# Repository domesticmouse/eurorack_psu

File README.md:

# Eurorack PSU

A simple 6HP +-12V Eurorack PSU, based on Winterbloom's [Micronova][].
See [EurorRack dimensions][] for faceplate dimensions.

[Micronova]: https://winterbloom.com/shop/micronova/
[EurorRack dimensions]: https://midisoft.de/EuroRackDimensions/EuroRack_Dimensions.html

## Parts

| LCSC Part | Manufacturer | Description |
| --- | --- | --- |
| [C72487](https://www.lcsc.com/product-detail/C72487.html) | ROQANG | CAP ALUM 10uF ±20% 50V SMD |
| [C3001207](https://www.lcsc.com/product-detail/C3001207.html) | ROQANG | CAP ALUM 22uF ±20% 25V SMD |
| [C1779](https://www.lcsc.com/product-detail/C1779.html) | Samsung Electro-Mechanics | CAP CER 4.7uF 25V X5R 0805 |
| [C3151829](https://www.lcsc.com/product-detail/C3151829.html) | ROQANG | CAP ALUM 100uF ±20% 50V SMD |
| [c701168](https://www.lcsc.com/product-detail/C701168.html) | muRata | FIXED IND 10uH 800mA 190mΩ SMD,3x3mm |
| [c64982](https://www.lcsc.com/product-detail/C64982.html) | MDD(Microdiode Semiconductor) | DIODE SCHOTTKY 40V SMA(DO-214AC) |
| [C5369648](https://www.lcsc.com/product-detail/C5369648.html) | YLPTEC | K7812-1000R3 SIP,11.5x7.6mm AC DC Configurable Power Supply Modules RoHS |
| [C22355851](https://www.lcsc.com/product-detail/C22355851.html) | DOWO | VARISTOR 18V 150A 1206 |
| [C142805](https://www.lcsc.com/product-detail/C142805.html) | Littelfuse | 24V 1.5A 20A 3A 40mΩ 1812 PTC Resettable Fuses RoHS |
| [C27834](https://www.lcsc.com/product-detail/C27834.html) | UNI-ROYAL | RES 5.1kΩ ±1% 125mW 0805 |
| [C84256](https://www.lcsc.com/product-detail/C84256.html) | NATIONSTAR | LED RED 0805 SMD |
| [C22373734](https://www.lcsc.com/product-detail/C22373734.html) | Hynetek | USB-C Power Receiver Controller 100W |
| [C1744](https://www.lcsc.com/product-detail/C1744.html) | FH | 50V 4.7nF X7R ±10% 0805 |
| [C1726](https://www.lcsc.com/product-detail/C1726.html) | FH | 50V 20nF X7R ±10% 0805 |
| [C52711227](https://www.lcsc.com/product-detail/C52711227.html) | HH | USB 2.0 5A Surface Mount Vertical 16P Female Type-C USB Connector |

## USB Type C PD Datasheets

- [C52711227 USB Connector](https://www.lcsc.com/datasheet/C52711227.pdf)
- [C22373734 USB Type-C Power Delivery Sink Controller](https://www.lcsc.com/datasheet/C22373734.pdf)

## Kicanvas

- [PSU](https://kicanvas.org/?github=https%3A%2F%2Fgithub.com%2Fdomesticmouse%2Feurorack_psu%2Fblob%2Fmain%2Fhardware%2FPSU%2FPSU.kicad_pro)
- [Faceplate](https://kicanvas.org/?github=https%3A%2F%2Fgithub.com%2Fdomesticmouse%2Feurorack_psu%2Fblob%2Fmain%2Fhardware%2Ffaceplate%2Ffaceplate.kicad_pro)

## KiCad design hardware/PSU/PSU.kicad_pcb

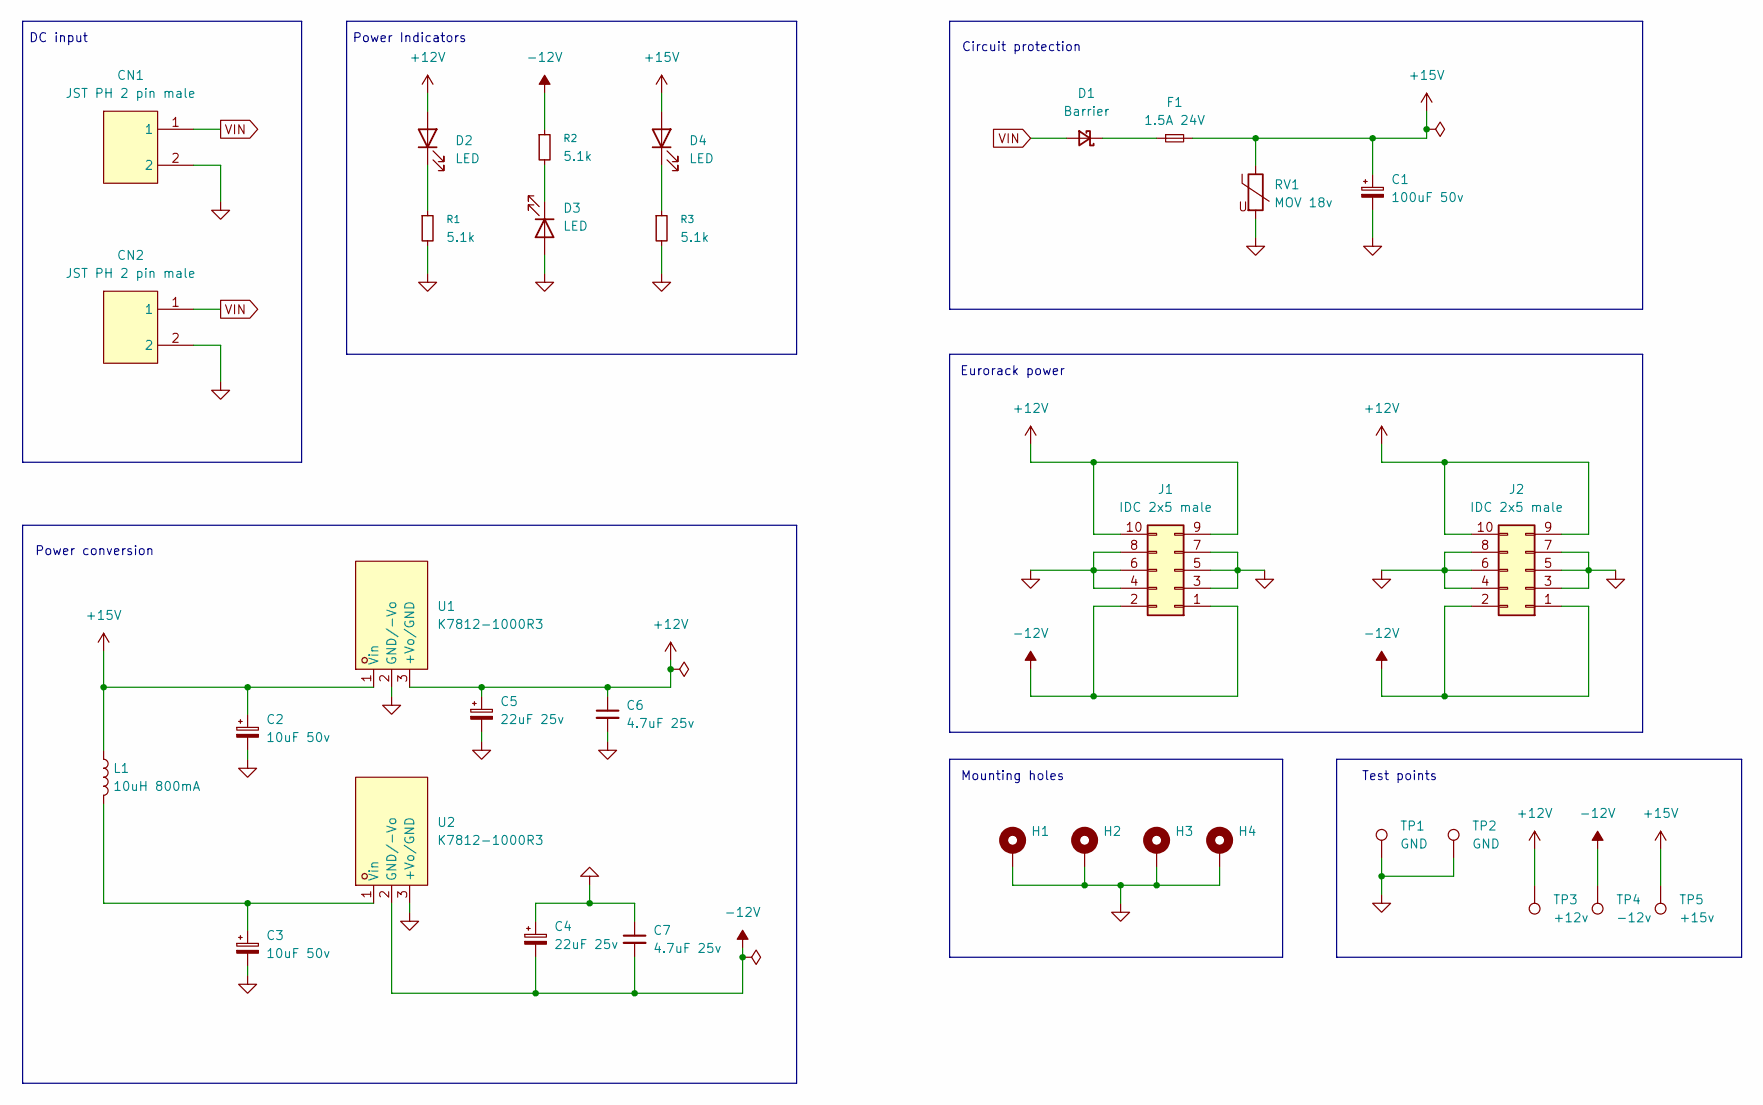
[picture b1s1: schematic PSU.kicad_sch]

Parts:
C1: 100uF 50v; CP_Elec_6.3x7.7; LCSC Part C3151829
C2, C3: 10uF 50v; CP_Elec_5x5.4; LCSC Part C72487
C4, C5: 22uF 25v; CP_Elec_5x5.4; LCSC Part C3001207
C6, C7: 4.7uF 25v; C_0805_2012Metric_Pad1.18x1.45mm_HandSolder; LCSC Part C1779
CN1, CN2: JST PH 2 pin male; CONN-TH_B2B-PH-K-S; LCSC Part C131337
D1: Barrier; D_SMA_Handsoldering; LCSC Part C64982
D2, D3, D4: LED; LED_D3.0mm; LCSC Part C84256
F1: 1.5A 24V; Fuse_1812_4532Metric_Pad1.30x3.40mm_HandSolder; LCSC Part C142805
H1, H2, H3, H4: MountingHole_3.2mm_M3_Pad
J1, J2: IDC 2x5 male; IDC-Header_2x05_P2.54mm_Vertical
L1: 10uH 800mA; L_muRata_LQH3NPZ100MMEL_HandSolder; LCSC Part C701168
R1, R2, R3: 5.1k; R_0805_2012Metric_Pad1.20x1.40mm_HandSolder; LCSC Part C27834
RV1: MOV 18v; R_1206_3216Metric_Pad1.30x1.75mm_HandSolder; LCSC Part C22355851
TP1, TP2: GND; TestPoint_Keystone_5000-5004_Miniature
TP3: +12v; TestPoint_Keystone_5000-5004_Miniature
TP4: -12v; TestPoint_Keystone_5000-5004_Miniature
TP5: +15v; TestPoint_Keystone_5000-5004_Miniature
U1, U2: K7812-1000R3; PWRM-TH_K7812-1000R3; LCSC Part C5369648

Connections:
+12V: C5.1, C6.1, D2.2 (A), J1.9, J1.10, J2.9, J2.10, TP3.1, U1.3 (+Vo/GND)
+15V: C1.1, C2.1, D4.2 (A), F1.2, L1.1, RV1.1, TP5.1, U1.1 (Vin)
-12V: C4.2, C7.2, J1.1, J1.2, J2.1, J2.2, R2.1, TP4.1, U2.2 (GND/-Vo)
GND: C1.2, C2.2, C3.2, C4.1, C5.2, C6.2, C7.1, CN1.2, CN2.2, D3.2 (A), H1.1, H2.1, H3.1, H4.1, J1.3, J1.4, J1.5, J1.6, J1.7, J1.8, J2.3, J2.4, J2.5, J2.6, J2.7, J2.8, R1.2, R3.2, RV1.2, TP1.1, TP2.1, U1.2 (GND/-Vo), U2.3 (+Vo/GND)
unnamed: D1.1 (K), F1.1
unnamed: D2.1 (K), R1.1
unnamed: D3.1 (K), R2.2
unnamed: D4.1 (K), R3.1
unnamed: C3.1, L1.2, U2.1 (Vin)
VIN: CN1.1, CN2.1, D1.2 (A)

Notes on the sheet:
Eurorack power
Circuit protection
Power Indicators
Test points
Mounting holes
DC input
Power conversion

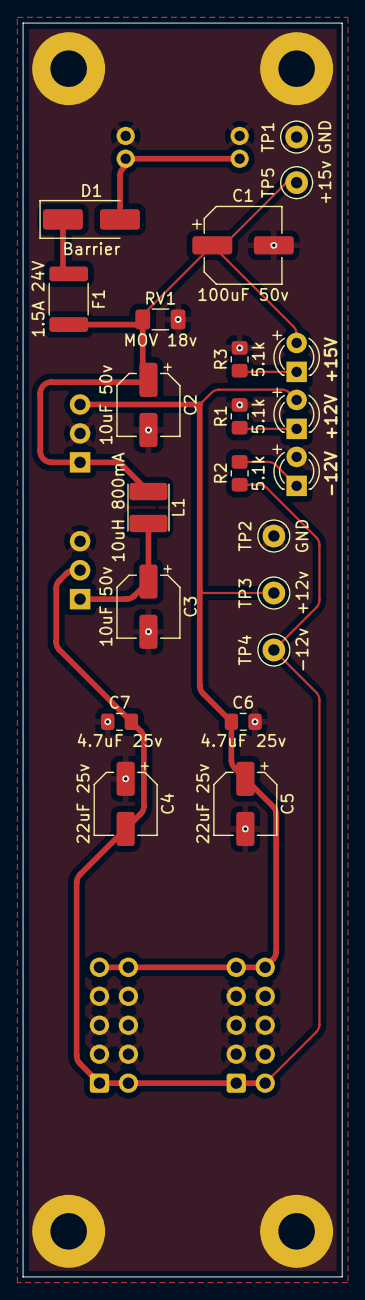
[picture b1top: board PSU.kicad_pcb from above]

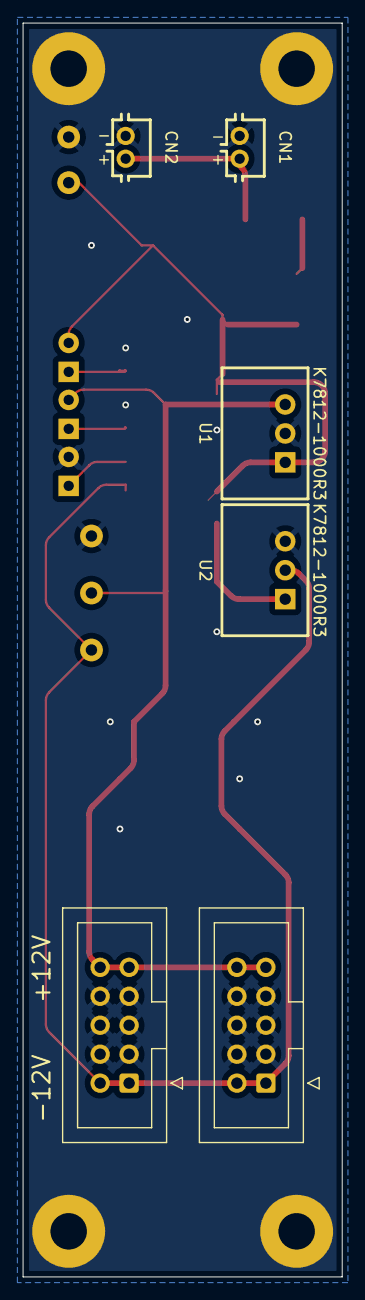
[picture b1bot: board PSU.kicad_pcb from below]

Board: 2 copper layers, 28.0 x 110.0 mm, 32 parts (6 on the bottom side), 10 nets.

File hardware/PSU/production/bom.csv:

Designator,Footprint,Quantity,Value,LCSC Part #
C1,CP_Elec_6.3x7.7,1,100uF 50v,C3151829
"C2, C3",CP_Elec_5x5.4,2,10uF 50v,C72487
"C4, C5",CP_Elec_5x5.4,2,22uF 25v,C3001207
"C6, C7",0805,2,4.7uF 25v,C1779
"CN1, CN2",CONN-TH_B2B-PH-K-S,2,JST PH 2 pin male,C131337
D1,D_SMA_Handsoldering,1,Barrier,C64982
"D2, D3, D4",LED_D3.0mm,3,LED,C84256
F1,1812,1,1.5A 24V,C142805
"J1, J2",IDC-Header_2x05_P2.54mm_Vertical,2,IDC 2x5 male,
L1,L_muRata_LQH3NPZ100MMEL_HandSolder,1,10uH 800mA,C701168
"R1, R2, R3",0805,3,5.1k,C27834
RV1,1206,1,MOV 18v,C22355851
"TP1, TP2",TestPoint_Keystone_5000-5004_Miniature,2,GND,
TP3,TestPoint_Keystone_5000-5004_Miniature,1,+12v,
TP4,TestPoint_Keystone_5000-5004_Miniature,1,-12v,
TP5,TestPoint_Keystone_5000-5004_Miniature,1,+15v,
"U1, U2",PWRM-TH_K7812-1000R3,2,K7812-1000R3,C5369648

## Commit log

2025-11-28 Add a README
2025-11-28 Initial KiCad files
2025-11-28 Initial schematic
2025-11-28 Initial board layout
2025-11-28 Add test points
2025-11-29 Use 3mm LEDs instead
2025-11-29 Build the production file
2025-11-30 faceplate init
2025-11-30 Update Faceplate
2025-11-30 Start of USB C PD implementation
2025-12-01 Update faceplate and hit print
2025-12-02 Add + markers
2025-12-10 Add Kicanvas section with PSU link to README
2025-12-10 Add Faceplate link to README
2025-12-10 Add more labels to the power input connections
